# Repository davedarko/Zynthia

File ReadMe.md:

See more at https://hackaday.io/project/5237-zynthia-sequencer-synthesizer

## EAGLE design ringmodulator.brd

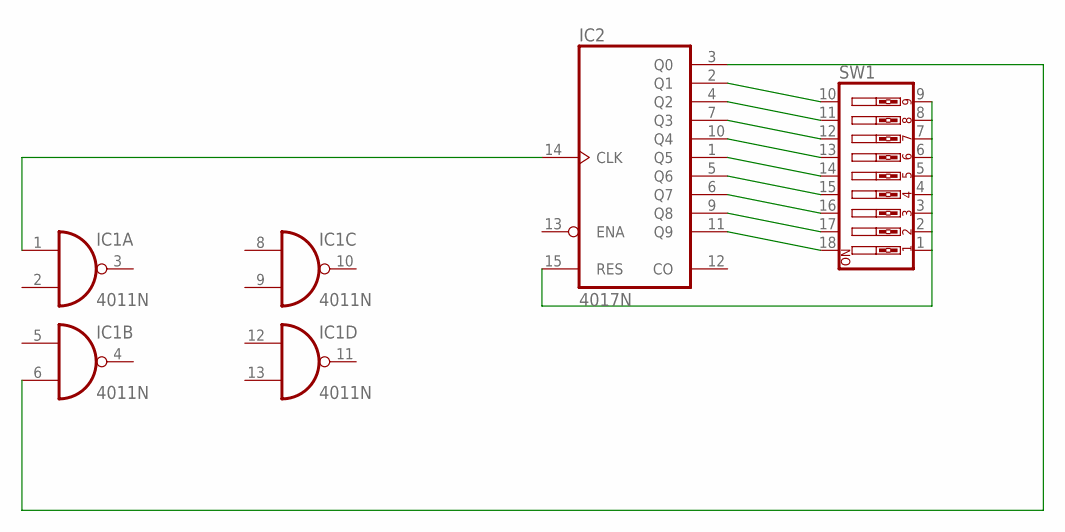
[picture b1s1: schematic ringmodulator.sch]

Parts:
IC1: 4011N; DIL14
IC2: 4017N; DIL16
SW1: SW_DIP-9; EDG-09

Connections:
unnamed: IC1.1 (I0), IC2.14 (CLK)
unnamed: IC1.6 (I1), IC2.3 (Q0)
unnamed: IC2.2 (Q1), SW1.10
unnamed: IC2.4 (Q2), SW1.11
unnamed: IC2.7 (Q3), SW1.12
unnamed: IC2.10 (Q4), SW1.13
unnamed: IC2.1 (Q5), SW1.14
unnamed: IC2.5 (Q6), SW1.15
unnamed: IC2.6 (Q7), SW1.16
unnamed: IC2.9 (Q8), SW1.17
unnamed: IC2.11 (Q9), SW1.18
unnamed: IC2.15 (RES), SW1.1, SW1.2, SW1.3, SW1.4, SW1.5, SW1.6, SW1.7, SW1.8, SW1.9
VDD: IC1.14 (VDD), IC2.16 (VDD)
VSS: IC1.7 (VSS), IC2.8 (VSS)

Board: 2 copper layers, 3 parts (0 on the bottom side), 14 nets, no tracks yet.

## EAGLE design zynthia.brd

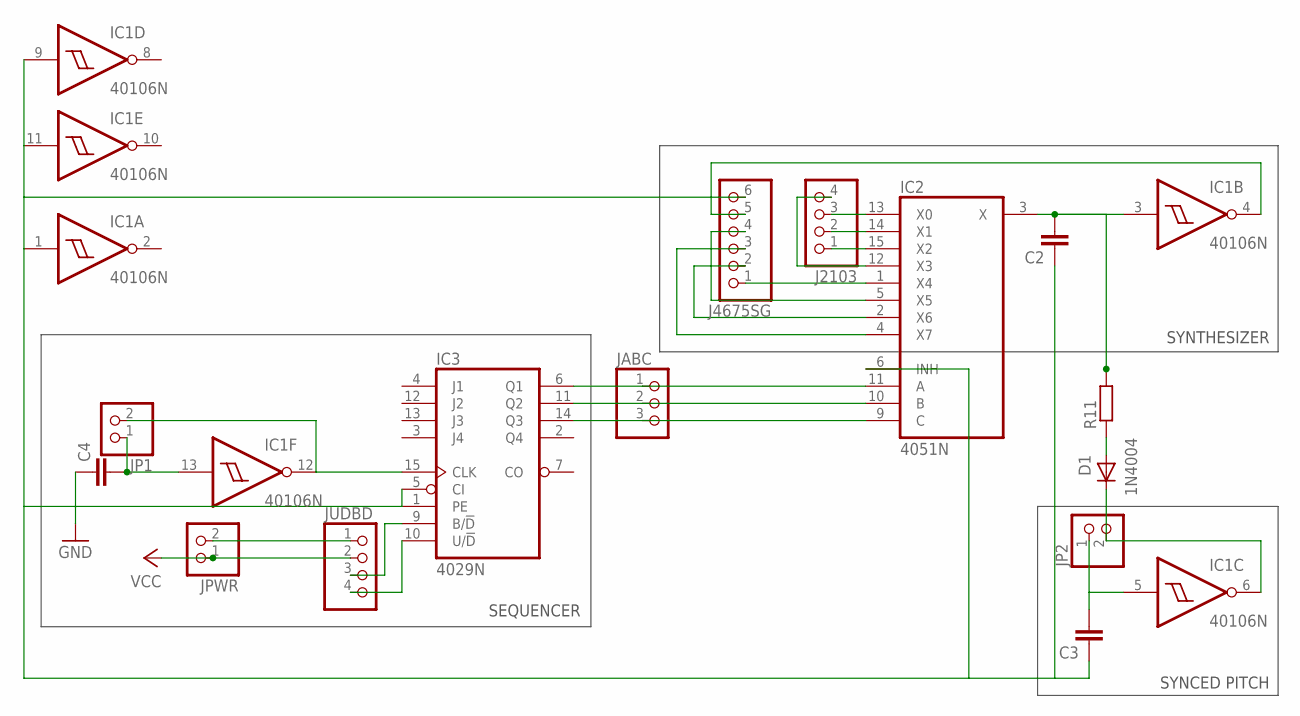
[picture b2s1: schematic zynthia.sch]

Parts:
C2, C3, C4: C-EU025-024X044; C025-024X044
D1: 1N4004; DO41-10
IC1: 40106N; DIL14
IC2: 4051N; DIL16
IC3: 4029N; DIL16
J2103: PINHD-1X4; 1X04
J4675SG: PINHD-1X6; 1X06
JABC: PINHD-1X3; 1X03
JP1, JP2: PINHD-1X2; 1X02
JPWR: PINHD-1X2; 1X02
JUDBD: PINHD-1X4; 1X04
R11: R-EU_0204/2V; 0204V

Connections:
GND: C4.1
unnamed: IC1.12 (O), IC3.15 (CLK), JP1.2
unnamed: C4.2, IC1.13 (I), JP1.1
unnamed: C2.2, IC1.3 (I), IC2.3 (X), R11.2
unnamed: C3.2, IC1.5 (I), JP2.1
unnamed: IC2.13 (X0), J2103.3
unnamed: IC3.10 (U/!D), JUDBD.4
unnamed: IC3.9 (B/!D), JUDBD.3
unnamed: IC2.9 (C), IC3.14 (Q3), JABC.3
unnamed: IC2.10 (B), IC3.11 (Q2), JABC.2
unnamed: IC2.11 (A), IC3.6 (Q1), JABC.1
unnamed: JPWR.2, JUDBD.1
unnamed: IC2.5 (X5), J4675SG.4
unnamed: IC2.1 (X4), J4675SG.1
unnamed: IC2.4 (X7), J4675SG.3
unnamed: IC1.4 (O), J4675SG.5
unnamed: IC2.15 (X2), J2103.1
unnamed: IC2.12 (X3), J2103.4
unnamed: D1.C, IC1.6 (O), JP2.2
unnamed: D1.A, R11.1
unnamed: IC2.2 (X6), J4675SG.2
unnamed: IC2.14 (X1), J2103.2
VCC: IC1.14 (VDD), IC2.16 (VCC), IC3.16 (VDD), JPWR.1, JUDBD.2
VEE: C2.1, C3.1, IC1.1 (I), IC1.7 (VSS), IC1.9 (I), IC1.11 (I), IC2.6 (INH), IC2.7 (VEE), IC2.8 (GND), IC3.1 (PE), IC3.5 (CI), IC3.8 (VSS), J4675SG.6

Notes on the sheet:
SYNCED PITCH
SEQUENCER
SYNTHESIZER

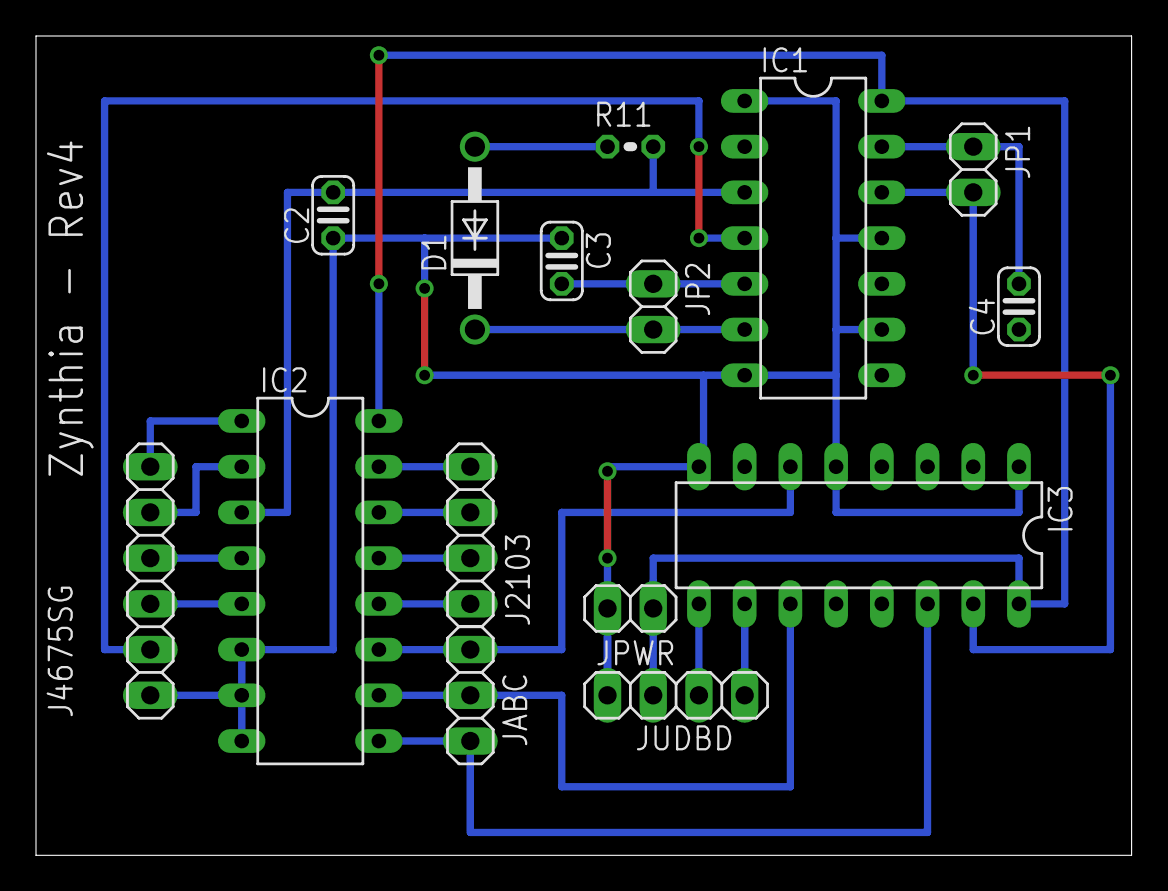
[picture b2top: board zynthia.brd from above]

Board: 2 copper layers, 60.9 x 45.5 mm, 15 parts (0 on the bottom side), 23 nets.

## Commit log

2015-04-22 Revision 5 (at least)
2015-04-22 link
2015-05-16 ring modulator
